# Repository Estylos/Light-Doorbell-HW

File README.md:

# Light Doorbell Hardware

This repository contains the KiCad design files (schematics and 4-layer circular PCB) for the Light Doorbell prototype: a **battery-powered, LED-signaling doorbell** based on a **STM32L051K8T6** microcontroller and **RFM69HCW** 433 MHz radio module.

A light doorbell is useful in many situations: notifying a user wearing headphones, assisting people with hearing impairments, or simply providing a silent visual alert...

## Overview

The prototype operates both as a transmitter and receiver.  
When the central button is pressed, it sends a coded message to another board listening on the same frequency. Upon receiving the message, the board flashes its dual-color LEDs, green or red, depending on the battery level.

The device is rechargeable via a USB-C connector, and works with a range of several tens of meters in open space.

## Features

- **Ultra-low-power STM32L051K8T6** ARM Cortex-M0+, 64 KB Flash, 8 KB RAM
- **RFM69HCW** 433 MHz transceiver module
- **Li-ion / Li-po battery** charger and management IC
- **3.0V LDO voltage regulator** to step down USB or battery voltage
- **Load sharing circuit** to seamlessly switch power source between USB and battery
- **Battery voltage monitoring**
- **433 MHz helical antenna**
- **Dual-color LEDs**, green and red for visual feedback
- **USB-C connector** for charging
- **Large mechanical push-button**
- **10-pin ARM SWD debug / programming port**
- **UART port** for optional serial communication
- **Multiple test points and jumpers** for current measurements, debug, and isolation
- Designed for **hand soldering** and **easy prototyping**
- Optimized for **low power consumption**

The current version focuses on development and testing. A future version could be further miniaturized by removing debug features and using smaller components...

## Related projects and documentation

- **[Light Doorbell SW](https://github.com/Estylos/Light-Doorbell-SW): Firmware of the project, based on the STM32 CubeHAL**  
- [STM32L051K8T6 Datasheet](https://www.st.com/en/microcontrollers-microprocessors/stm32l051k8.html)  
- [RFM69HCW Datasheet](https://cdn.sparkfun.com/datasheets/Wireless/General/RFM69HCW-V1.1.pdf)  
- [Adafruit Feather M0 Radio with RFM69 Packet Radio](https://learn.adafruit.com/adafruit-feather-m0-radio-with-rfm69-packet-radio/overview)  
- [Microchip (AN1149) - Designing A Li-Ion Battery Charger and Load Sharing System With Microchip’s Stand-Alone Li-Ion Battery Charge Management Controller](https://ww1.microchip.com/downloads/en/appnotes/01149c.pdf)  
- [Zak’s Electronics Blog - A Lithium Battery Charger with Load Sharing.](https://blog.zakkemble.net/a-lithium-battery-charger-with-load-sharing/)  
- [Hackaday - Embed with Elliot: Debounce your Noisy Buttons, Part I.](https://hackaday.com/2015/12/09/embed-with-elliot-debounce-your-noisy-buttons-part-i/)  
- [RefCircruit - Standard Simplest Battery Voltage Monitoring Circuit. ](https://refcircuit.com/articles/854-standard-simplest-battery-voltage-monitoring-circuit-engineering-schematic-solutions.html)

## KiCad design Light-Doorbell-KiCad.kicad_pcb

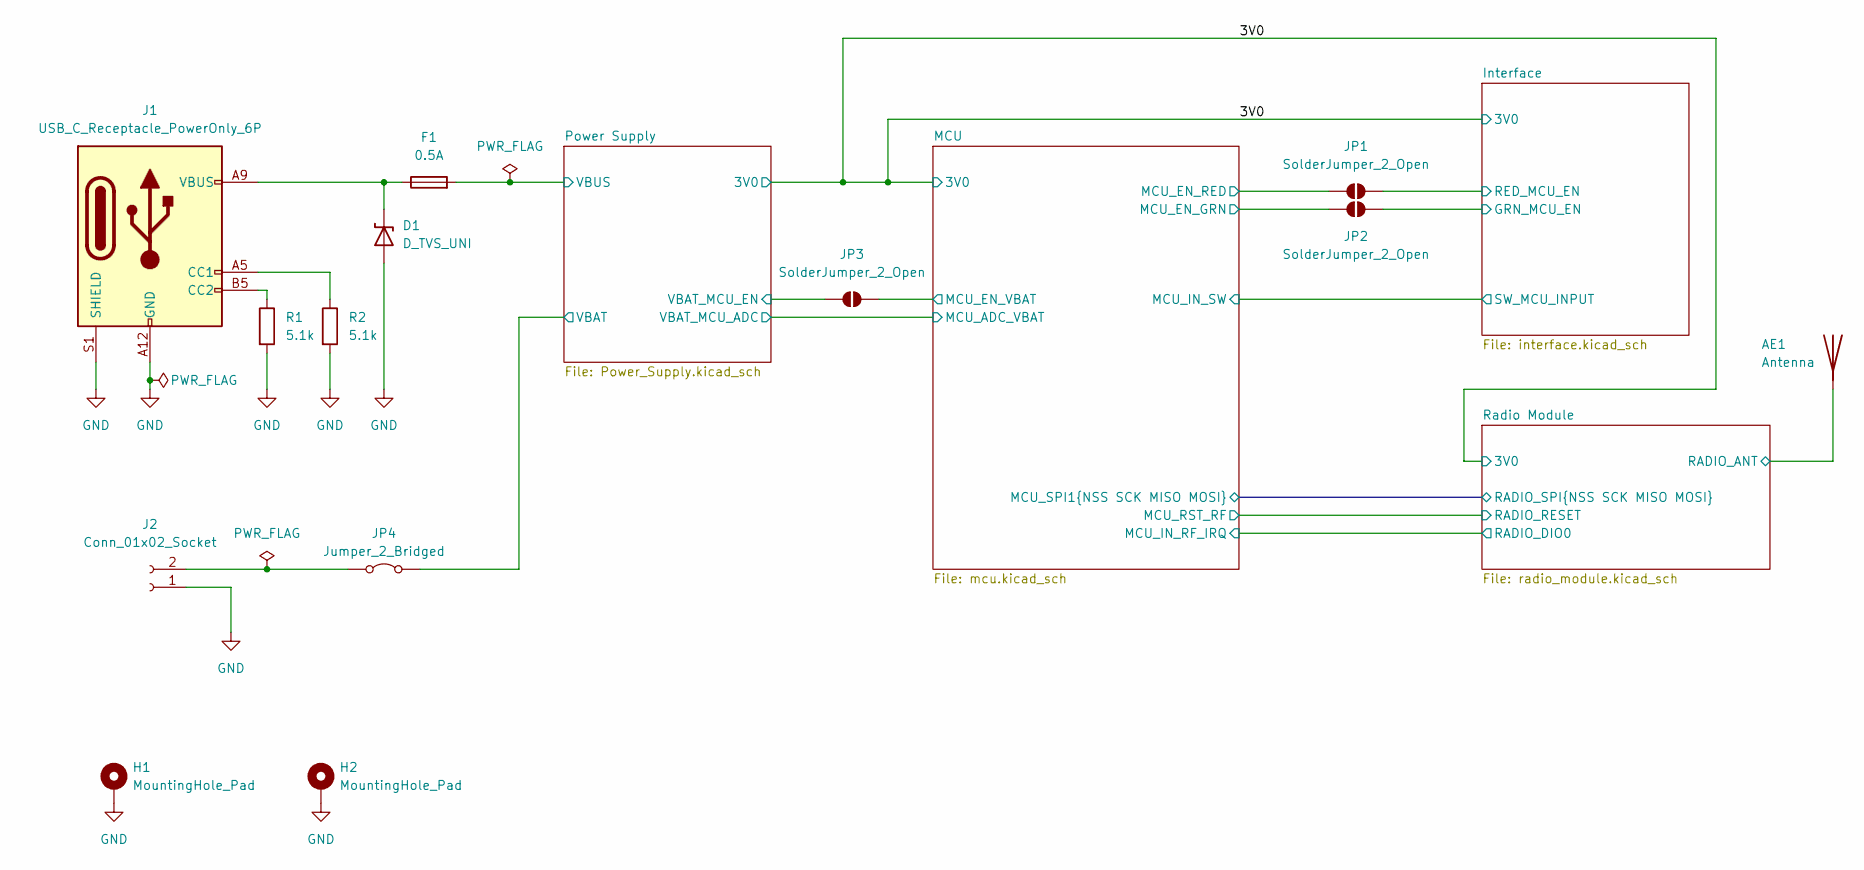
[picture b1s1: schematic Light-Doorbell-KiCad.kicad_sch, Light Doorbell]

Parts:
AE1: Antenna; THTPad_D2.0mm_Drill1.0mm; LCSC C718844
D1: D_TVS_UNI; D_SOD-323_HandSoldering; LCSC C552583
F1: 0.5A; Fuse_0805_2012Metric_Pad1.15x1.40mm_HandSolder; LCSC C2892412
H1, H2: MountingHole_Pad; MountingHole_2.2mm_M2_Pad
J1: USB_C_Receptacle_PowerOnly_6P; USB_C_Receptacle_GCT_USB4125-xx-x_6P_TopMnt_Horizontal; LCSC C668623
J2: Conn_01x02_Socket; PinHeader_1x02_P2.54mm_Vertical; LCSC C131337
JP1, JP2, JP3: SolderJumper_2_Open; SolderJumper-2_P1.3mm_Open_RoundedPad1.0x1.5mm
JP4: Jumper_2_Bridged; PinHeader_1x02_P2.54mm_Vertical
R1, R2: 5.1k; R_0805_2012Metric_Pad1.20x1.40mm_HandSolder; LCSC C2930296

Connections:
/Interface/GRN_MCU_EN: JP2.2 (B); also elsewhere on the board
/Interface/RED_MCU_EN: JP1.2 (B); also elsewhere on the board
/MCU/MCU_EN_GRN: JP2.1 (A); also elsewhere on the board
/MCU/MCU_EN_RED: JP1.1 (A); also elsewhere on the board
/MCU/MCU_EN_VBAT: JP3.2 (B); also elsewhere on the board
/Power Supply/VBAT: JP4.2 (B); also elsewhere on the board
/Power Supply/VBAT_MCU_EN: JP3.1 (A); also elsewhere on the board
/Power Supply/VBUS: F1.2; also elsewhere on the board
/Radio Module/RADIO_ANT: AE1.1 (A); also elsewhere on the board
GND: D1.2 (A2), H1.1, H2.1, J1.A12 (GND), J1.B12 (GND), J1.S1 (SHIELD), J2.1, R1.2, R2.2; also elsewhere on the board
unnamed: D1.1 (A1), F1.1, J1.A9 (VBUS), J1.B9 (VBUS)
unnamed: J1.A5 (CC1), R2.1
unnamed: J1.B5 (CC2), R1.1
unnamed: J2.2, JP4.1 (A)

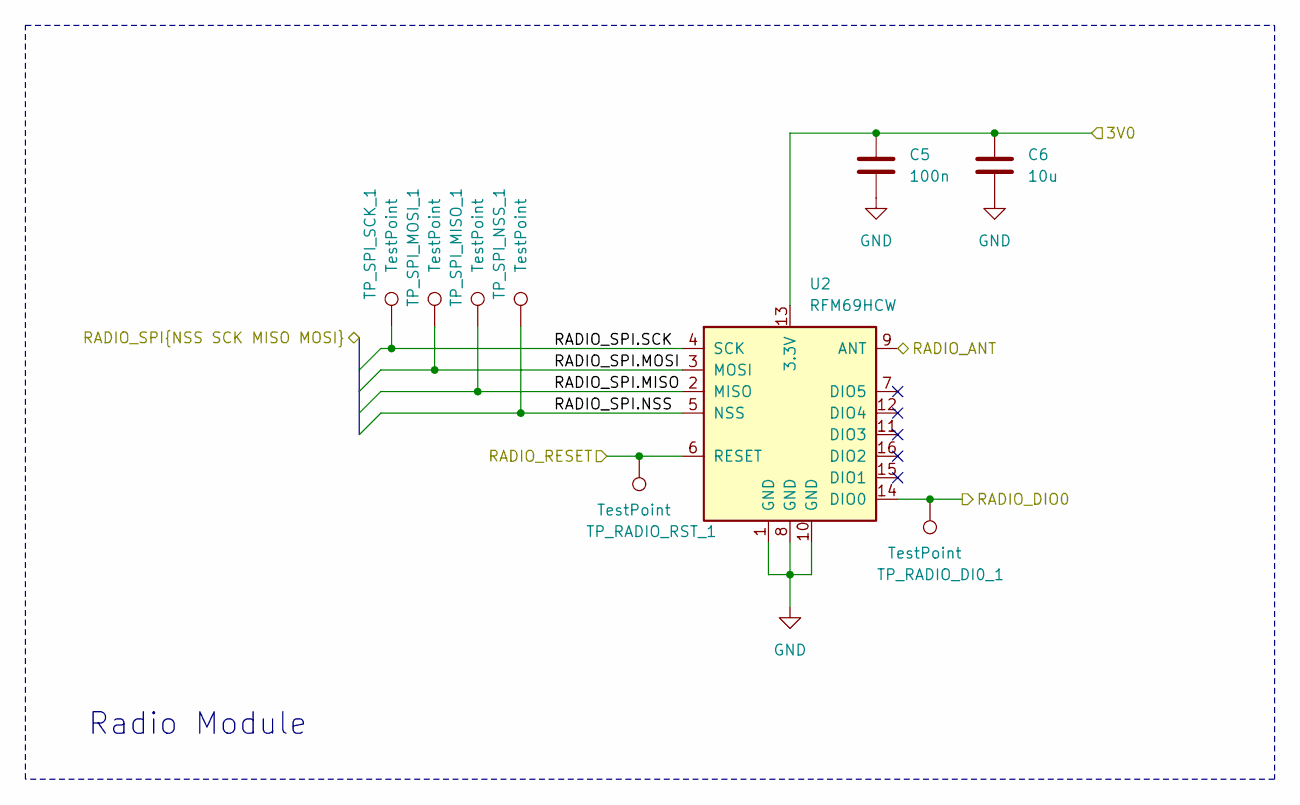
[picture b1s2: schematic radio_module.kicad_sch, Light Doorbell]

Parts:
C5: 100n; C_0805_2012Metric_Pad1.18x1.45mm_HandSolder; LCSC C1711
C6: 10u; C_0805_2012Metric_Pad1.18x1.45mm_HandSolder; LCSC C17024
TP_RADIO_DI0_1: TestPoint; TestPoint_Pad_D2.0mm
TP_RADIO_RST_1: TestPoint; TestPoint_Pad_D2.0mm
TP_SPI_MISO_1: TestPoint; TestPoint_Pad_D2.0mm
TP_SPI_MOSI_1: TestPoint; TestPoint_Pad_D2.0mm
TP_SPI_NSS_1: TestPoint; TestPoint_Pad_D2.0mm
TP_SPI_SCK_1: TestPoint; TestPoint_Pad_D2.0mm
U2: RFM69HCW; HOPERF_RFM9CW_SMD

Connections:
/3V0: C5.1, C6.1, U2.13 (3.3V); also elsewhere on the board
/MCU/MCU_IN_RF_IRQ: TP_RADIO_DI0_1.1, U2.14 (DIO0); also elsewhere on the board
/MCU/MCU_RST_RF: TP_RADIO_RST_1.1, U2.6 (RESET); also elsewhere on the board
/MCU/MCU_SPI1.MISO: TP_SPI_MISO_1.1, U2.2 (MISO); also elsewhere on the board
/MCU/MCU_SPI1.MOSI: TP_SPI_MOSI_1.1, U2.3 (MOSI); also elsewhere on the board
/MCU/MCU_SPI1.NSS: TP_SPI_NSS_1.1, U2.5 (NSS); also elsewhere on the board
/MCU/MCU_SPI1.SCK: TP_SPI_SCK_1.1, U2.4 (SCK); also elsewhere on the board
/Radio Module/RADIO_ANT: U2.9 (ANT); also elsewhere on the board
GND: C5.2, C6.2, U2.1 (GND), U2.8 (GND), U2.10 (GND); also elsewhere on the board

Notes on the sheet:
Radio Module

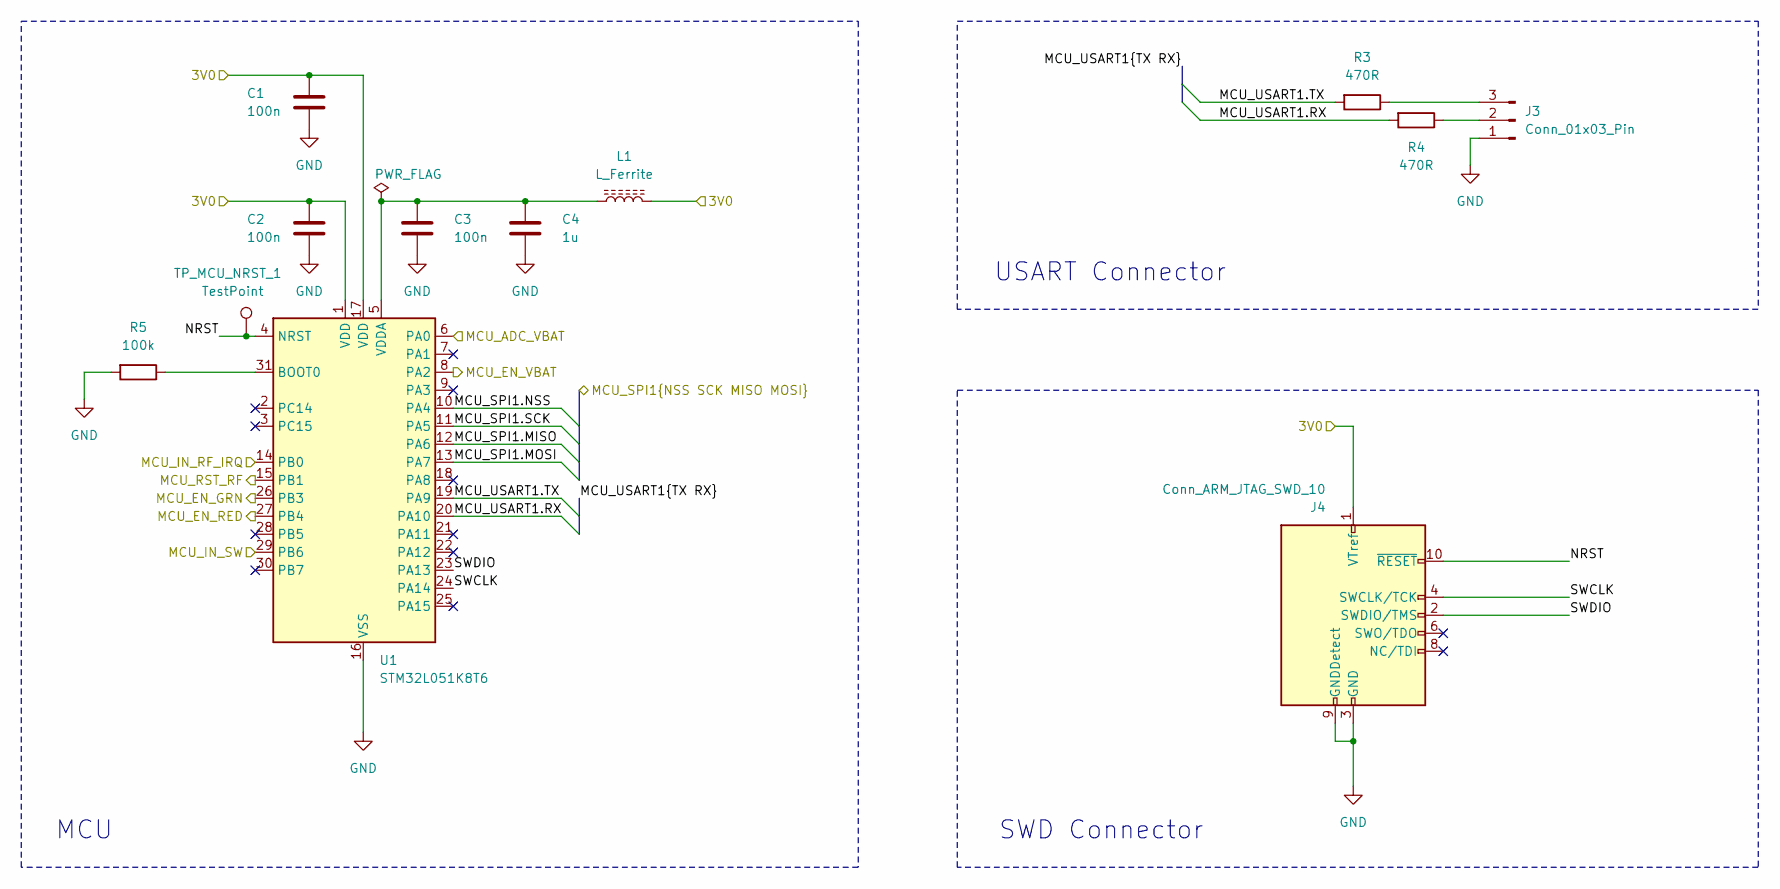
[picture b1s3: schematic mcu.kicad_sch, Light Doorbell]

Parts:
C1, C2, C3: 100n; C_0805_2012Metric_Pad1.18x1.45mm_HandSolder; LCSC C1711
C4: 1u; C_0805_2012Metric_Pad1.18x1.45mm_HandSolder; LCSC C2798196
J3: Conn_01x03_Pin; PinHeader_1x03_P2.54mm_Vertical
J4: Conn_ARM_JTAG_SWD_10; FTSH-105-01-L-DV-K; LCSC C448647
L1: L_Ferrite; L_0805_2012Metric_Pad1.05x1.20mm_HandSolder; LCSC C85835
R3, R4: 470R; R_0805_2012Metric_Pad1.20x1.40mm_HandSolder; LCSC C2907329
R5: 100k; R_0805_2012Metric_Pad1.20x1.40mm_HandSolder; LCSC C25611
TP_MCU_NRST_1: TestPoint; TestPoint_Pad_D2.0mm
U1: STM32L051K8T6; LQFP-32_7x7mm_P0.8mm; LCSC C915970

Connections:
/3V0: C1.1, C2.1, J4.1 (VTref), L1.2, U1.1 (VDD), U1.17 (VDD); also elsewhere on the board
/Interface/SW_MCU_INPUT: U1.29 (PB6); also elsewhere on the board
/MCU/MCU_ADC_VBAT: U1.6 (PA0); also elsewhere on the board
/MCU/MCU_EN_GRN: U1.26 (PB3); also elsewhere on the board
/MCU/MCU_EN_RED: U1.27 (PB4); also elsewhere on the board
/MCU/MCU_EN_VBAT: U1.8 (PA2); also elsewhere on the board
/MCU/MCU_IN_RF_IRQ: U1.14 (PB0); also elsewhere on the board
/MCU/MCU_RST_RF: U1.15 (PB1); also elsewhere on the board
/MCU/MCU_SPI1.MISO: U1.12 (PA6); also elsewhere on the board
/MCU/MCU_SPI1.MOSI: U1.13 (PA7); also elsewhere on the board
/MCU/MCU_SPI1.NSS: U1.10 (PA4); also elsewhere on the board
/MCU/MCU_SPI1.SCK: U1.11 (PA5); also elsewhere on the board
/MCU/MCU_USART1.RX: R4.2, U1.20 (PA10)
/MCU/MCU_USART1.TX: R3.2, U1.19 (PA9)
/MCU/NRST: J4.10 (~RESET), TP_MCU_NRST_1.1, U1.4 (NRST)
/MCU/SWCLK: J4.4 (SWCLK/TCK), U1.24 (PA14)
/MCU/SWDIO: J4.2 (SWDIO/TMS), U1.23 (PA13)
GND: C1.2, C2.2, C3.2, C4.2, J3.1, J4.3 (GND), J4.5 (GND), J4.9 (GNDDetect), R5.2, U1.16 (VSS), U1.32 (VSS); also elsewhere on the board
unnamed: J3.2, R4.1
unnamed: J3.3, R3.1
unnamed: R5.1, U1.31 (BOOT0)
unnamed: C3.1, C4.1, L1.1, U1.5 (VDDA)

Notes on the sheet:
USART Connector
MCU
SWD Connector

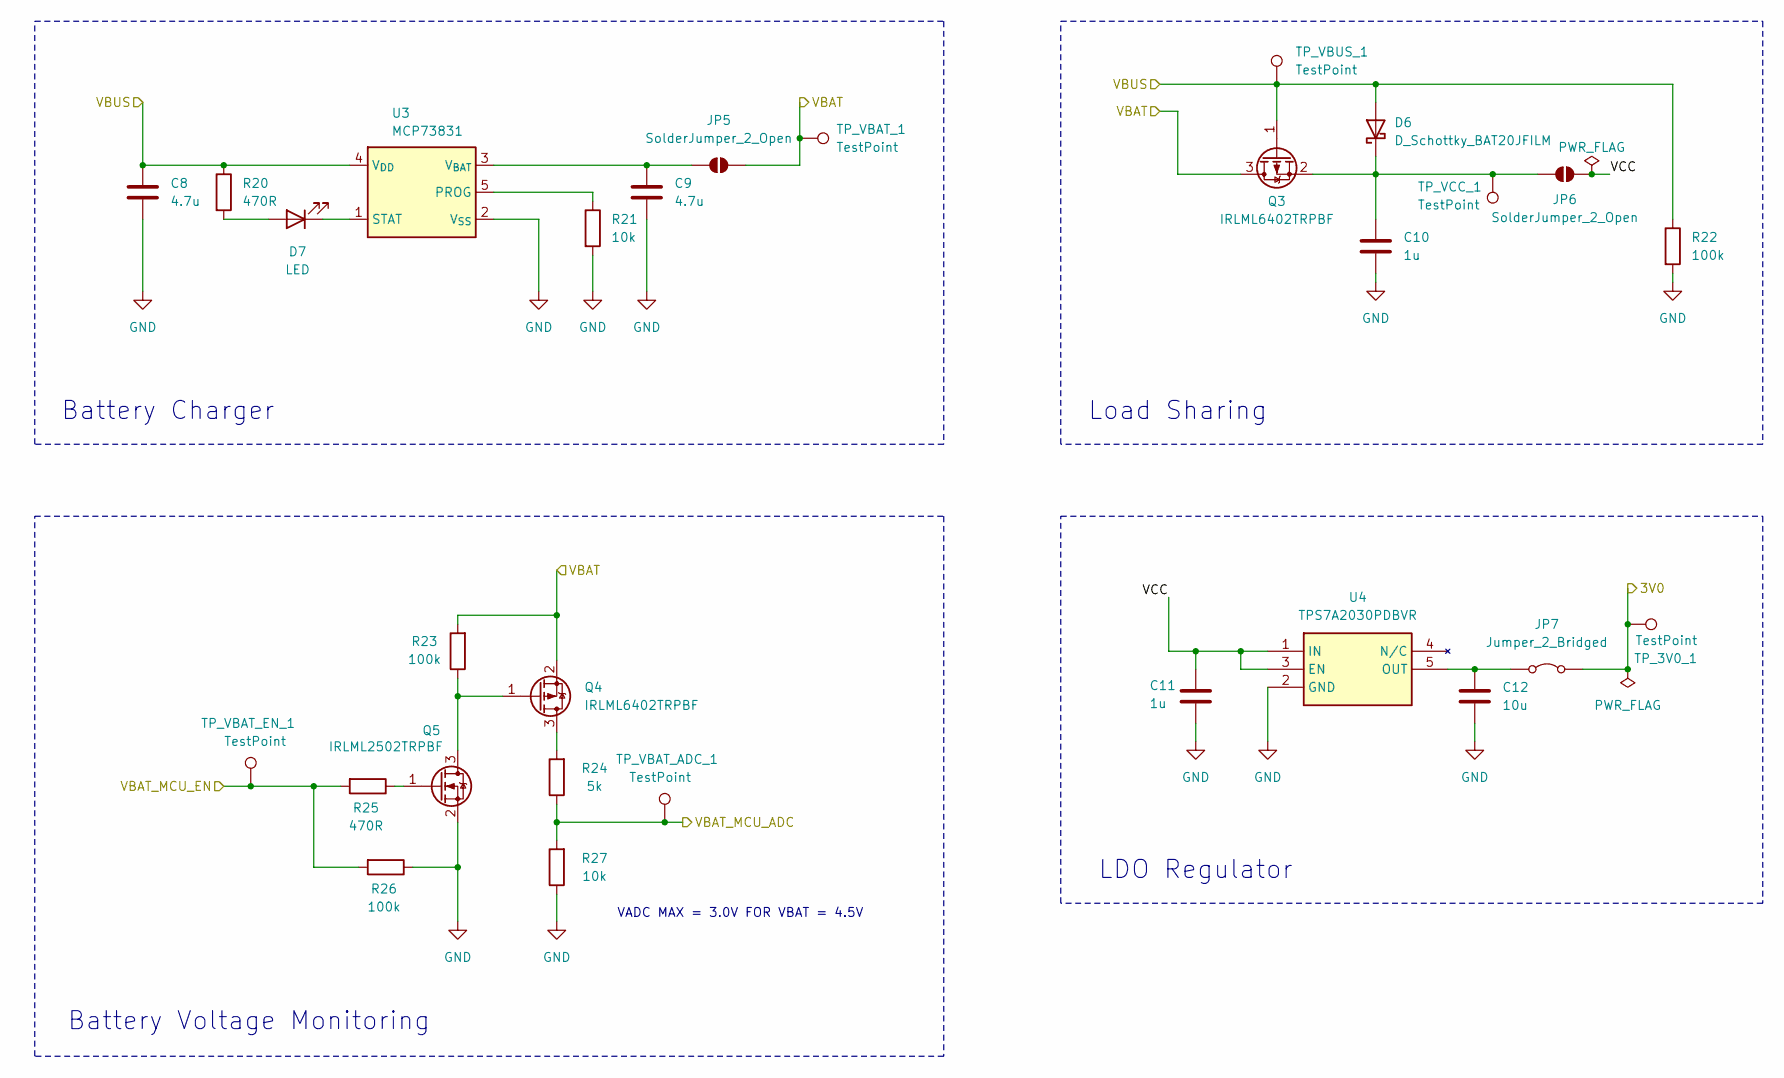
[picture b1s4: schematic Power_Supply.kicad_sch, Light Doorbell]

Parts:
C8, C9: 4.7u; C_0805_2012Metric_Pad1.18x1.45mm_HandSolder; LCSC C1779
C10, C11: 1u; C_0805_2012Metric_Pad1.18x1.45mm_HandSolder; LCSC C2798196
C12: 10u; C_0805_2012Metric_Pad1.18x1.45mm_HandSolder; LCSC C17024
D6: D_Schottky_BAT20JFILM; D_SOD-323_HandSoldering; LCSC C155590
D7: LED; LED_0805_2012Metric_Pad1.15x1.40mm_HandSolder; LCSC C434431
JP5, JP6: SolderJumper_2_Open; SolderJumper-2_P1.3mm_Open_RoundedPad1.0x1.5mm
JP7: Jumper_2_Bridged; PinHeader_1x02_P2.54mm_Vertical
Q3, Q4: IRLML6402TRPBF; SOT-23_Handsoldering; LCSC C2593
Q5: IRLML2502TRPBF; SOT-23_Handsoldering; LCSC C2589
R20, R25: 470R; R_0805_2012Metric_Pad1.20x1.40mm_HandSolder; LCSC C2907329
R21, R27: 10k; R_0805_2012Metric_Pad1.20x1.40mm_HandSolder; LCSC C17414
R22, R23, R26: 100k; R_0805_2012Metric_Pad1.20x1.40mm_HandSolder; LCSC C25611
R24: 5k; R_0805_2012Metric_Pad1.20x1.40mm_HandSolder; LCSC C2828783
TP_3V0_1: TestPoint; TestPoint_Pad_D2.0mm
TP_VBAT_1: TestPoint; TestPoint_Pad_D2.0mm
TP_VBAT_ADC_1: TestPoint; TestPoint_Pad_D2.0mm
TP_VBAT_EN_1: TestPoint; TestPoint_Pad_D2.0mm
TP_VBUS_1: TestPoint; TestPoint_Pad_D2.0mm
TP_VCC_1: TestPoint; TestPoint_Pad_D2.0mm
U3: MCP73831; TSOT-23-5_HandSoldering; LCSC C424093
U4: TPS7A2030PDBVR; TSOT-23-5_HandSoldering; LCSC C963429

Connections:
/3V0: JP7.2 (B), TP_3V0_1.1; also elsewhere on the board
/MCU/MCU_ADC_VBAT: R24.1, R27.2, TP_VBAT_ADC_1.1; also elsewhere on the board
/Power Supply/VBAT: JP5.2 (B), Q3.3 (D), Q4.2 (S), R23.2, TP_VBAT_1.1; also elsewhere on the board
/Power Supply/VBAT_MCU_EN: R25.2, R26.2, TP_VBAT_EN_1.1; also elsewhere on the board
/Power Supply/VBUS: C8.1, D6.2 (A), Q3.1 (G), R20.1, R22.1, TP_VBUS_1.1, U3.4 (V_{DD}); also elsewhere on the board
/Power Supply/VCC: C11.1, JP6.2 (B), U4.1 (IN), U4.3 (EN)
GND: C8.2, C9.2, C10.2, C11.2, C12.2, Q5.2 (S), R21.2, R22.2, R26.1, R27.1, U3.2 (V_{SS}), U4.2 (GND); also elsewhere on the board
unnamed: C10.1, D6.1 (K), JP6.1 (A), Q3.2 (S), TP_VCC_1.1
unnamed: D7.2 (A), R20.2
unnamed: D7.1 (K), U3.1 (STAT)
unnamed: C9.1, JP5.1 (A), U3.3 (V_{BAT})
unnamed: C12.1, JP7.1 (A), U4.5 (OUT)
unnamed: Q4.3 (D), R24.2
unnamed: Q4.1 (G), Q5.3 (D), R23.1
unnamed: Q5.1 (G), R25.1
unnamed: R21.1, U3.5 (PROG)

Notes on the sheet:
Battery Voltage Monitoring
Load Sharing
Battery Charger
VADC MAX = 3.0V FOR VBAT = 4.5V
LDO Regulator

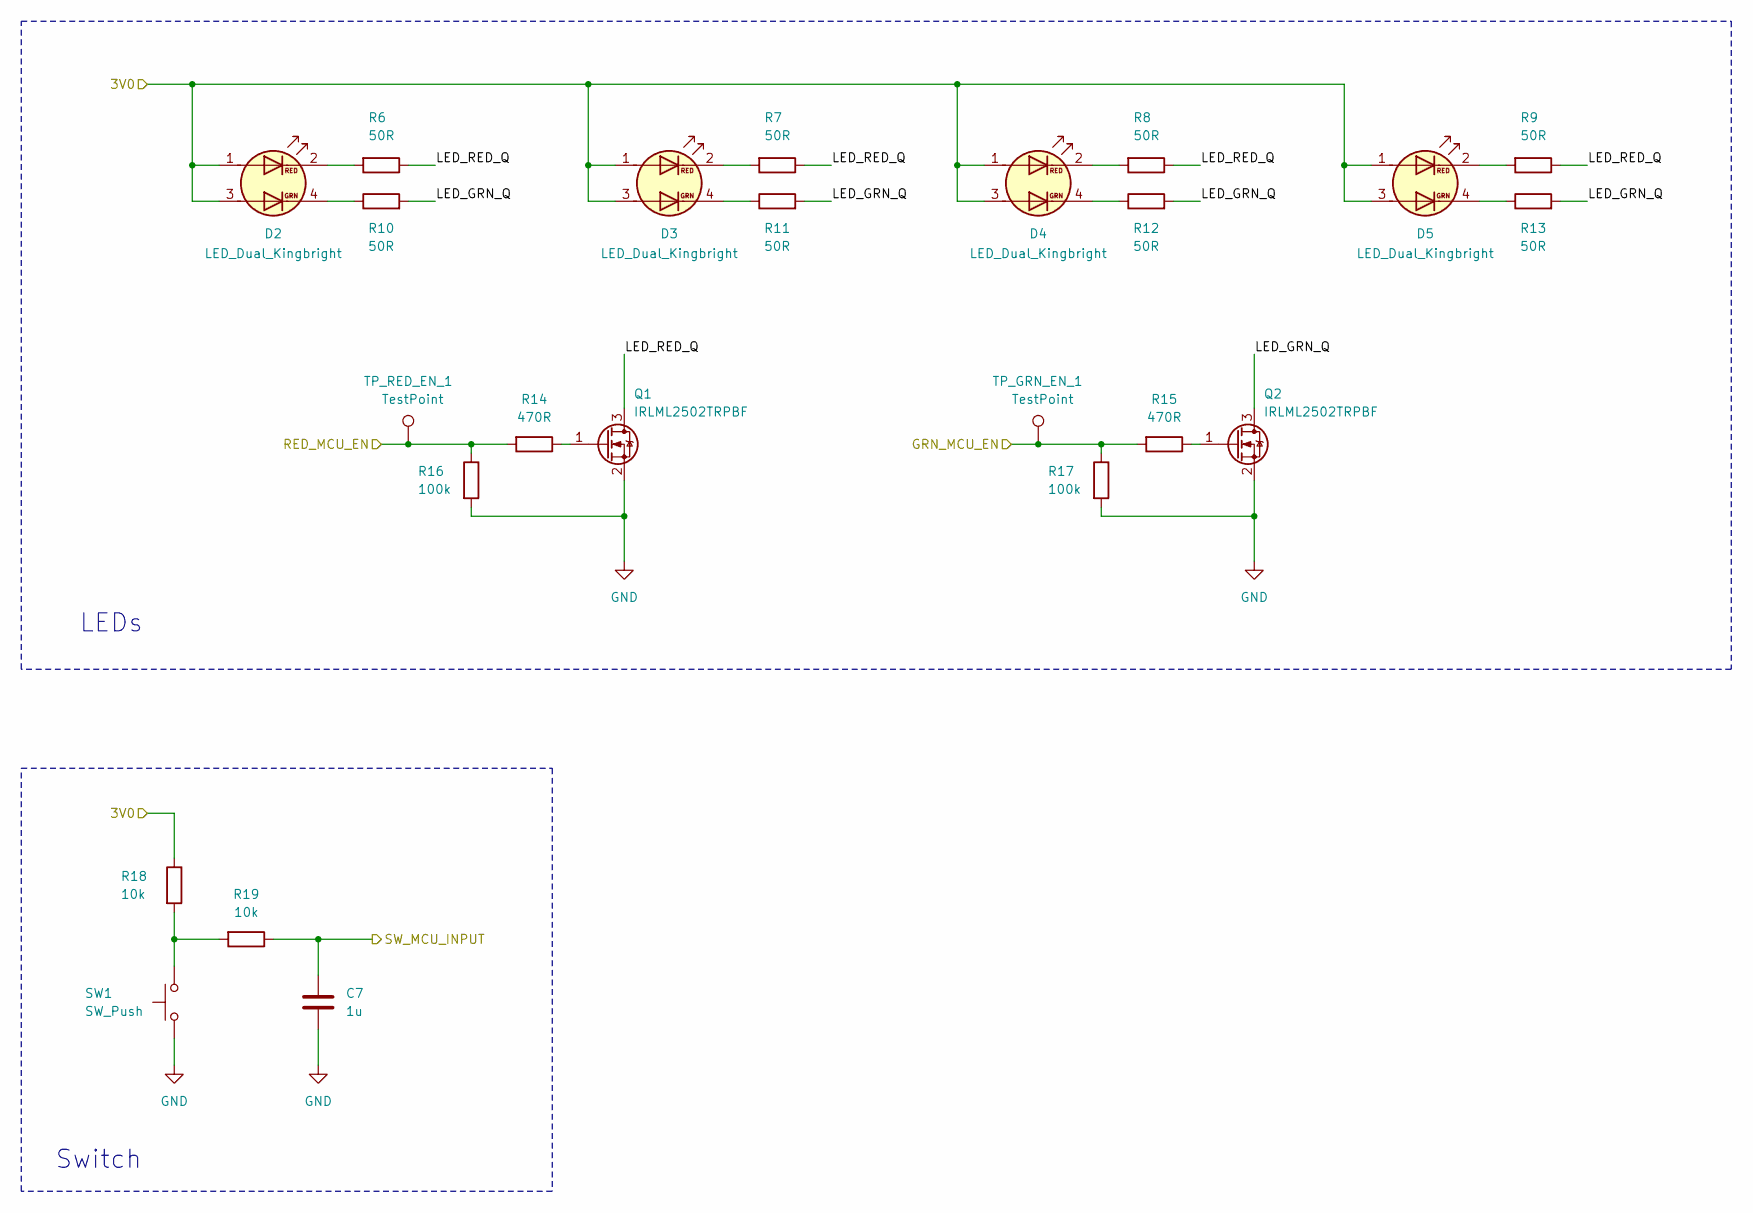
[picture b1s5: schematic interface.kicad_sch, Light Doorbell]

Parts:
C7: 1u; C_0805_2012Metric_Pad1.18x1.45mm_HandSolder; LCSC C2798196
D2, D3, D4, D5: LED_Dual_Kingbright; LED_Kingbright_KPBD-3224; LCSC C598328
Q1, Q2: IRLML2502TRPBF; SOT-23_Handsoldering; LCSC C2589
R6, R7, R8, R9, R10, R11, R12, R13: 50R; R_0805_2012Metric_Pad1.20x1.40mm_HandSolder; LCSC C2828866
R14, R15: 470R; R_0805_2012Metric_Pad1.20x1.40mm_HandSolder; LCSC C2907329
R16, R17: 100k; R_0805_2012Metric_Pad1.20x1.40mm_HandSolder; LCSC C25611
R18, R19: 10k; R_0805_2012Metric_Pad1.20x1.40mm_HandSolder; LCSC C17414
SW1: SW_Push; LCSC C455234
TP_GRN_EN_1: TestPoint; TestPoint_Pad_D2.0mm
TP_RED_EN_1: TestPoint; TestPoint_Pad_D2.0mm

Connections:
/3V0: D2.1 (A1), D2.3 (A2), D3.1 (A1), D3.3 (A2), D4.1 (A1), D4.3 (A2), D5.1 (A1), D5.3 (A2), R18.1; also elsewhere on the board
/Interface/GRN_MCU_EN: R15.2, R17.1, TP_GRN_EN_1.1; also elsewhere on the board
/Interface/LED_GRN_Q: Q2.3 (D), R10.2, R11.2, R12.2, R13.2
/Interface/LED_RED_Q: Q1.3 (D), R6.1, R7.1, R8.1, R9.1
/Interface/RED_MCU_EN: R14.2, R16.1, TP_RED_EN_1.1; also elsewhere on the board
/Interface/SW_MCU_INPUT: C7.1, R19.1; also elsewhere on the board
GND: C7.2, Q1.2 (S), Q2.2 (S), R16.2, R17.2, SW1.1; also elsewhere on the board
unnamed: D2.2 (K1), R6.2
unnamed: D2.4 (K2), R10.1
unnamed: D3.2 (K1), R7.2
unnamed: D3.4 (K2), R11.1
unnamed: D4.2 (K1), R8.2
unnamed: D4.4 (K2), R12.1
unnamed: D5.2 (K1), R9.2
unnamed: D5.4 (K2), R13.1
unnamed: Q1.1 (G), R14.1
unnamed: Q2.1 (G), R15.1
unnamed: R18.2, R19.2, SW1.2

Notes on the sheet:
Switch
LEDs

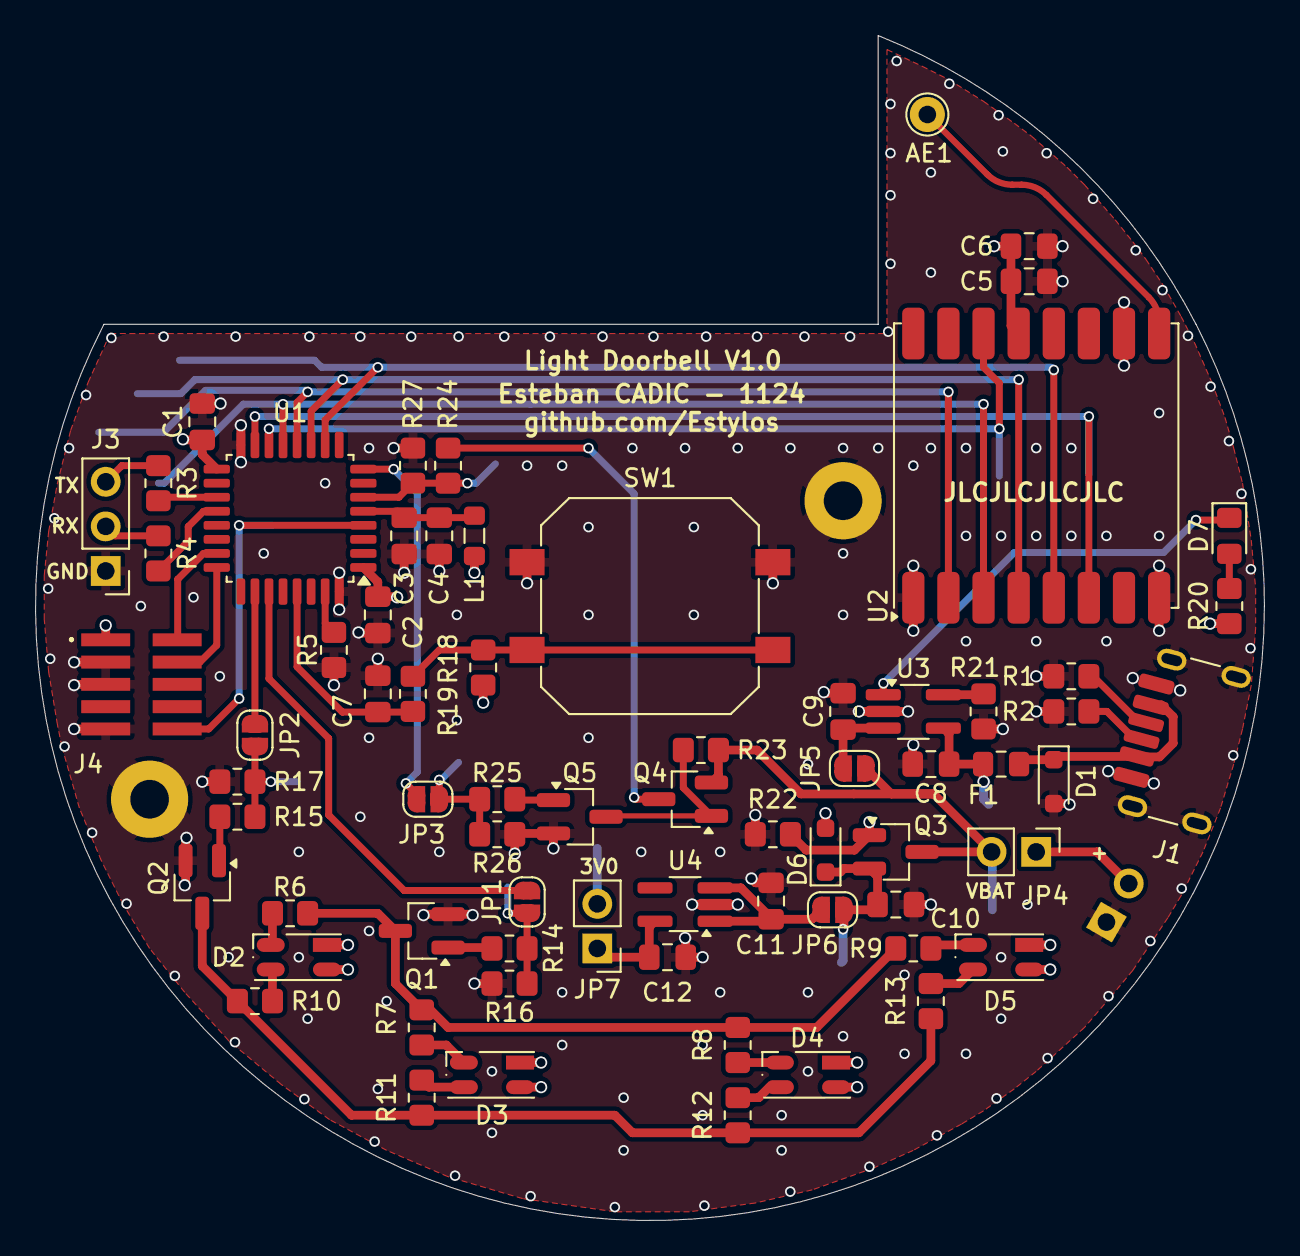
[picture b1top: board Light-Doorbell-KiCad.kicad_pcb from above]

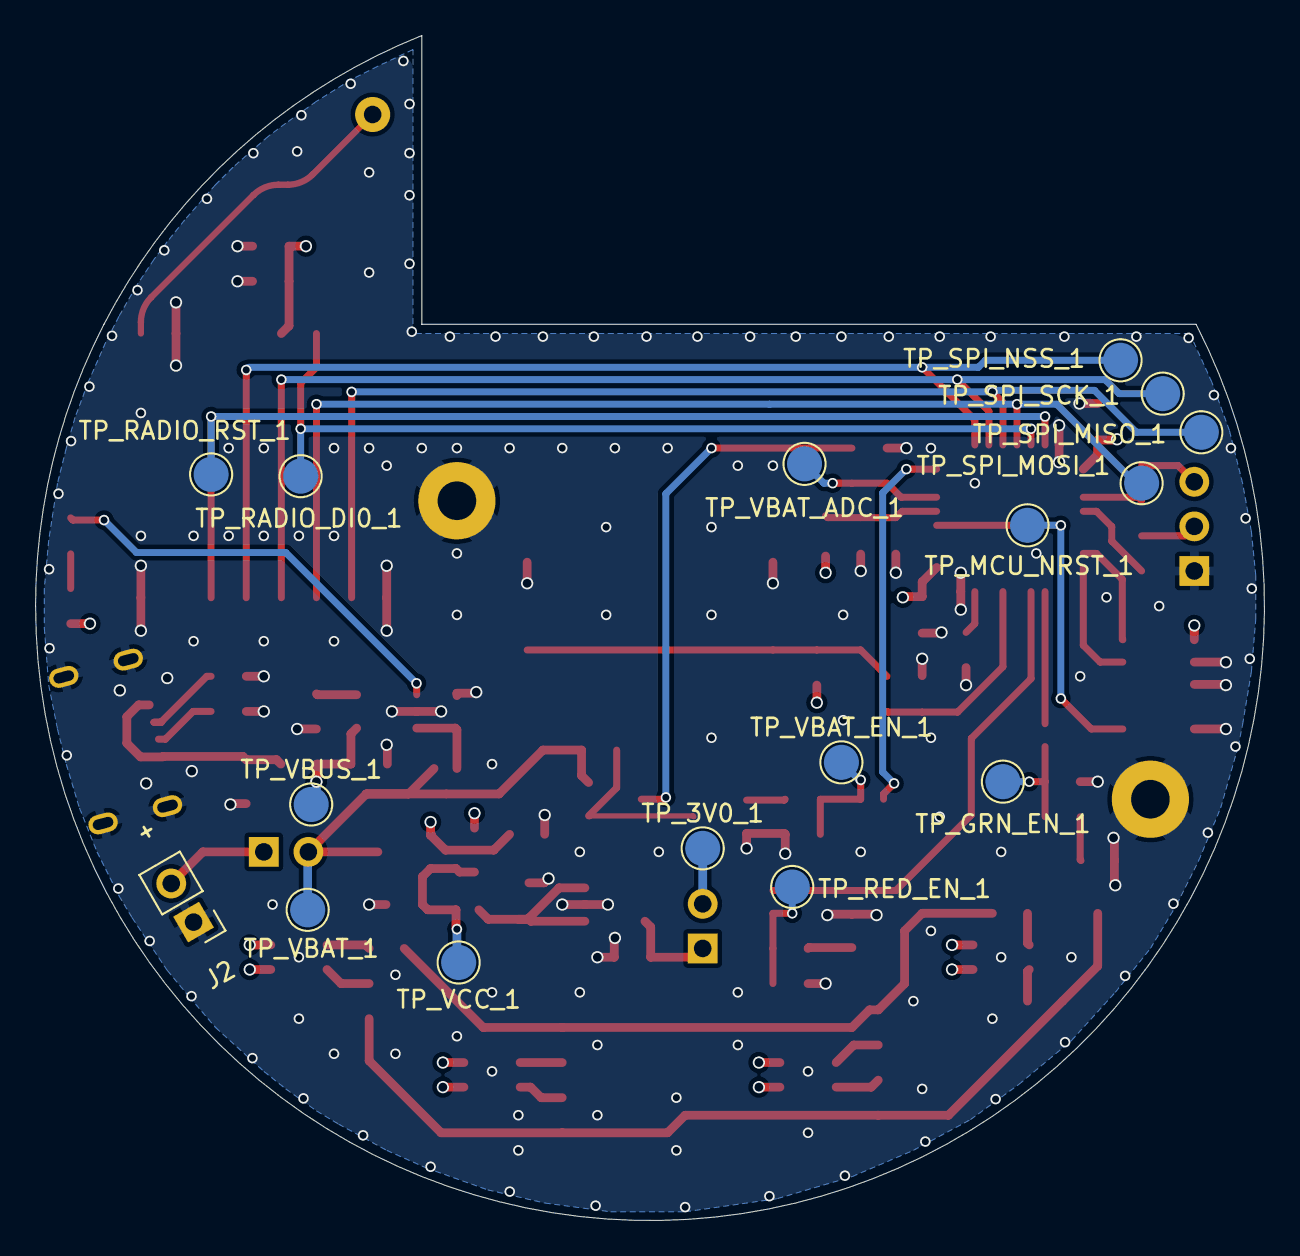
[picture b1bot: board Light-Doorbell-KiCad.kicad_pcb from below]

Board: 4 copper layers, 70.0 x 67.5 mm, 87 parts (16 on the bottom side), 55 nets.

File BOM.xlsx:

Reference | Value | LCSC | Footprint | Description | Datasheet | Qty
AE1 | Antenna | C718844 | PRJ_FOOTPRINTS:THTPad_D2.0mm_Drill1.0mm | Spring Antenna 433 MHz | ~ | 1
C1,C2,C3,C5 | 100n | C1711 | PRJ_FOOTPRINTS:C_0805_2012Metric_Pad1.18x1.45mm_HandSolder | Unpolarized capacitor | ~ | 4
C4,C7,C10,C11 | 1u | C2798196 | PRJ_FOOTPRINTS:C_0805_2012Metric_Pad1.18x1.45mm_HandSolder | Unpolarized capacitor | ~ | 4
C6,C12 | 10u | C17024 | PRJ_FOOTPRINTS:C_0805_2012Metric_Pad1.18x1.45mm_HandSolder | Unpolarized capacitor | ~ | 2
C8,C9 | 4.7u | C1779 | PRJ_FOOTPRINTS:C_0805_2012Metric_Pad1.18x1.45mm_HandSolder | Unpolarized capacitor | ~ | 2
D1 | D_TVS_UNI | C552583 | PRJ_FOOTPRINTS:D_SOD-323_HandSoldering | Uni ESD protection PESD5V0U1UA,115, 6.8V Vbr, IEC61000−4−2 Level 4 | https://assets.nexperia.com/documents/data-sheet/PESD5V0U1UA.pdf | 1
D2,D3,D4,D5 | LED_Dual_Kingbright | C598328 | PRJ_FOOTPRINTS:LED_Kingbright_KPBD-3224 | Dual LED, red, green-yellow, 20°, SMD | https://www.lcsc.com/datasheet/lcsc_datasheet_2008121136_Kin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 | 4
D6 | D_Schottky_BAT20JFILM | C155590 | PRJ_FOOTPRINTS:D_SOD-323_HandSoldering | Schottky diode, ST BAT20JFILM, 1A If, 23V Vrrm | https://eu.mouser.com/datasheet/2/389/bat20j-1849045.pdf | 1
D7 | LED | C434431 | PRJ_FOOTPRINTS:LED_0805_2012Metric_Pad1.15x1.40mm_HandSolder | Light emitting diode | ~ | 1
F1 | 0.5A | C2892412 | PRJ_FOOTPRINTS:Fuse_0805_2012Metric_Pad1.15x1.40mm_HandSolder | Fuse 0.5A, KUU K0805L050BR, 0805 | https://www.lcsc.com/datasheet/lcsc_datasheet_2109071730_KUU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 | 1
J1 | USB_C_Receptacle_PowerOnly_6P | C668623 | PRJ_FOOTPRINTS:USB_C_Receptacle_GCT_USB4125-xx-x_6P_TopMnt_Horizontal | USB Power-Only 6P Type-C Receptacle connector | https://www.lcsc.com/datasheet/lcsc_datasheet_2006181823_SHO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 | 1
J2 | Conn_01x02_Socket | C131337 | PRJ_FOOTPRINTS:PinHeader_1x02_P2.54mm_Vertical | Generic connector, single row, 01x02, script generated | ~ | 1
J3 | Conn_01x03_Pin |  | PRJ_FOOTPRINTS:PinHeader_1x03_P2.54mm_Vertical | Generic connector, single row, 01x03, script generated | ~ | 1
J4 | Conn_ARM_JTAG_SWD_10 | C448647 | PRJ_FOOTPRINTS:FTSH-105-01-L-DV-K | Cortex Debug Connector, standard ARM Cortex-M SWD and JTAG interface | http://infocenter.arm.com/help/topic/com.arm.doc.ddi0314h/DD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 | 1
JP4,JP7 | Jumper_2_Bridged |  | PRJ_FOOTPRINTS:PinHeader_1x02_P2.54mm_Vertical | Jumper, 2-pole, closed/bridged | ~ | 2
L1 | L_Ferrite | C85835 | PRJ_FOOTPRINTS:L_0805_2012Metric_Pad1.05x1.20mm_HandSolder | Ferrite Beads, 280mΩ ±25%, 1kΩ@100MHz, 0805 | ~ | 1
Q1,Q2,Q5 | IRLML2502TRPBF | C2589 | PRJ_FOOTPRINTS:SOT-23_Handsoldering | N-Channel MOSFET, 20V Vds, 4.2A Id, 45 mΩ Rds(on), SOT-23 | https://www.infineon.com/dgdl/irlml2502pbf-1.pdf?fileId=5546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 | 3
Q3,Q4 | IRLML6402TRPBF | C2593 | PRJ_FOOTPRINTS:SOT-23_Handsoldering | P-Channel MOSFET, -20V Vds, -3.7A Id, 65mΩ Rds(on), SOT-23 | https://www.infineon.com/dgdl/irlml6402pbf.pdf?fileId=5546d4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 | 2
R1,R2 | 5.1k | C2930296 | PRJ_FOOTPRINTS:R_0805_2012Metric_Pad1.20x1.40mm_HandSolder | Resistor | ~ | 2
R3,R4,R14,R15,R20,R25 | 470R | C2907329 | PRJ_FOOTPRINTS:R_0805_2012Metric_Pad1.20x1.40mm_HandSolder | Resistor | ~ | 6
R5,R16,R17,R22,R23,R26 | 100k | C25611 | PRJ_FOOTPRINTS:R_0805_2012Metric_Pad1.20x1.40mm_HandSolder | Resistor | ~ | 6
R6,R7,R8,R9,R10,R11,R12,R13 | 50R | C2828866 | PRJ_FOOTPRINTS:R_0805_2012Metric_Pad1.20x1.40mm_HandSolder | Resistor | ~ | 8
R18,R19,R21,R27 | 10k | C17414 | PRJ_FOOTPRINTS:R_0805_2012Metric_Pad1.20x1.40mm_HandSolder | Resistor | ~ | 4
R24 | 5k | C2828783 | PRJ_FOOTPRINTS:R_0805_2012Metric_Pad1.20x1.40mm_HandSolder | Resistor | ~ | 1
SW1 | SW_Push | C455234 | PRJ_FOOTPRINTS:SW_Push | Push button switch, generic, two pins | https://www.lcsc.com/datasheet/lcsc_datasheet_1912111437_XUN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 | 1
TP_3V0_1,TP_GRN_EN_1,TP_MCU_NRST_1,TP_RADIO_DI0_1,TP_RADIO_RST_1,TP_RED_EN_1,TP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 | TestPoint |  | PRJ_FOOTPRINTS:TestPoint_Pad_D2.0mm | test point | ~ | 15
U1 | STM32L051K8T6 | C915970 | PRJ_FOOTPRINTS:LQFP-32_7x7mm_P0.8mm | STMicroelectronics Arm Cortex-M0+ MCU, 32-64KB flash, 8KB RAM, 32 MHz, 1.65-3.6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 | https://eu.mouser.com/datasheet/2/389/stm32l051c6-1851259.pdf | 1
U2 | RFM69HCW |  | PRJ_FOOTPRINTS:HOPERF_RFM9CW_SMD | ISM radio transceiver, SoM | https://cdn.sparkfun.com/datasheets/Wireless/General/RFM69HC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 | 1
U3 | MCP73831 | C424093 | PRJ_FOOTPRINTS:TSOT-23-5_HandSoldering | Single cell Li-Ion/Li-Po charge management controller, 4.20V, SOT23-5 | https://ww1.microchip.com/downloads/en/DeviceDoc/MCP73831-Fa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 | 1
U4 | TPS7A2030PDBVR | C963429 | PRJ_FOOTPRINTS:TSOT-23-5_HandSoldering | LDO Voltage Regulators, 300-mA, ultra-low-noise, low-IQ, SOT23-5 | https://www.ti.com/lit/ds/symlink/tps7a20.pdf | 1

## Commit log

2025-04-19 Added KiCad files
2025-04-20 Added README file
    Added README file
